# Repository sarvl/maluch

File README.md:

## mALUch - 16 bit simple CPU

mALUch is a simple 16 bit cpu, created mostly as a design exercise 

## Running Simulation and Compiling Tools
To compile simulator it is necessary to have ncurses installed  

```bash
cd Soft/Simulator
make
```

To run a file it's as simple as
```bash
./simulate path/to/file
```

## Assembler  
To use assembler it is necessary to have fasmg installed

The assembler is implemented as a fasmg .inc file, so to write your own program you have to have `include "path/to/maluch.inc"` included in your file.  
To just do `include "maluch.inc"` make sure to add the path to maluch.inc to an environment variable called INCLUDE.

To compile a program do
```bash
fasmg main.asm [output]
```
The output name is optional, the default is the name of the input file sans the extension.

## Physical Implementation
work in progress 😎

## Software Implementation
in Simulator/  
  
mostly straightforward implementation with no interesting quirks, type `help` for list of commands, use `tab` to switch between COMMANDS window and SCREEN window.

## Authors
[@sarvl](https://github.com/sarvl)  
[@Racuun](https://github.com/Racuun)

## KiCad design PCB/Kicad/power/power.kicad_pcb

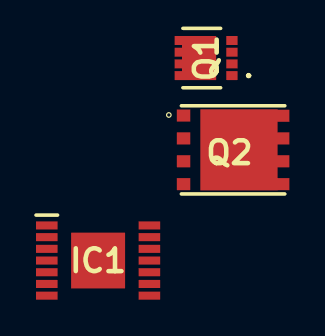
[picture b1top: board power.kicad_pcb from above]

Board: 2 copper layers, 3 parts (0 on the bottom side), 4 nets, no tracks yet.

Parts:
IC1: LM3150MH_NOPB; SOP65P640X110-15L
Q1: CSD17308Q3
Q2: CSD18531Q5A; Q5A

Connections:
unnamed: IC1.11 (HG), Q1.4 (G)
unnamed: IC1.13 (LG), Q2.4 (G)
unnamed: IC1.10 (SW), Q1.1 (S_1), Q1.2 (S_2), Q1.3 (S_3), Q2.5 (D_1), Q2.6 (D_2), Q2.7 (D_3), Q2.8 (D_4)
unnamed: Q2.1 (S_1), Q2.2 (S_2), Q2.3 (S_3)

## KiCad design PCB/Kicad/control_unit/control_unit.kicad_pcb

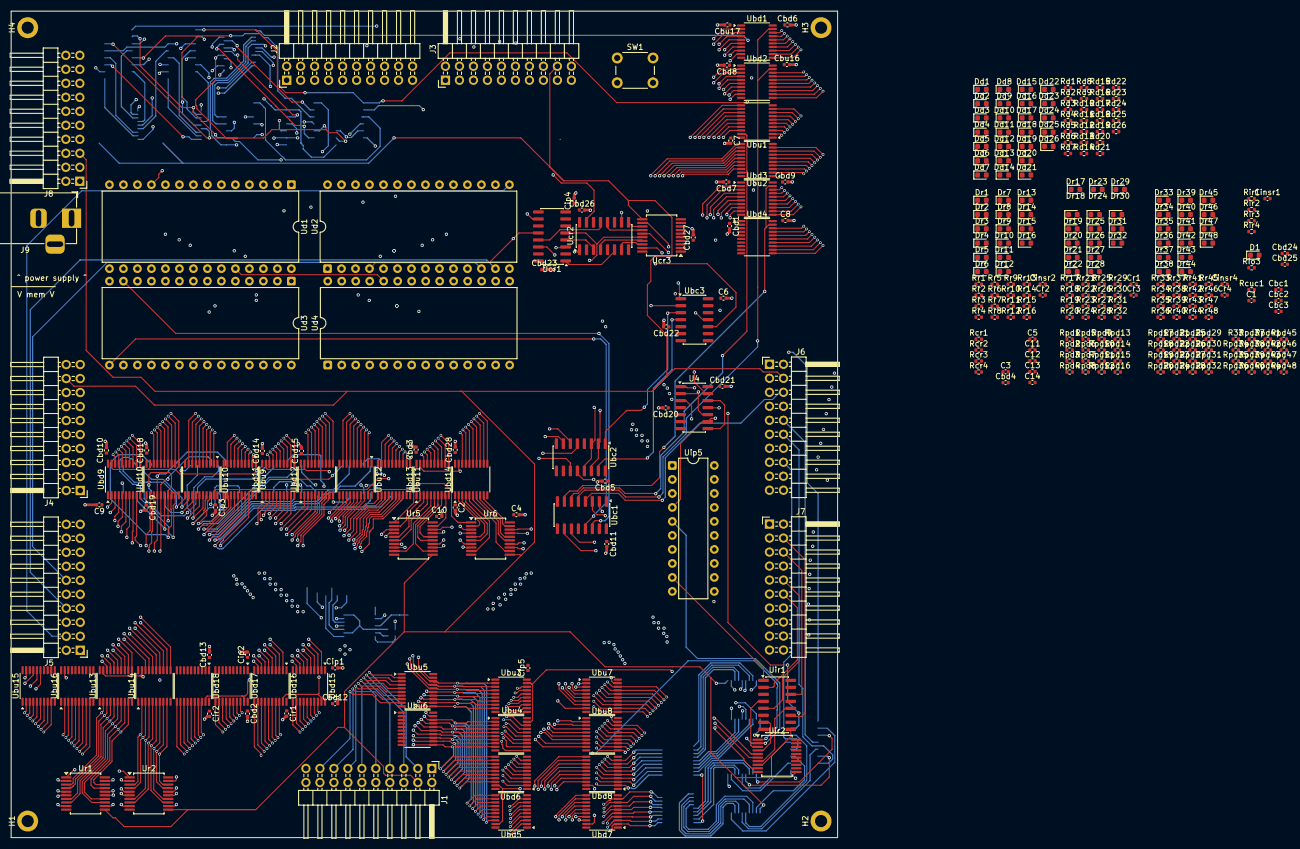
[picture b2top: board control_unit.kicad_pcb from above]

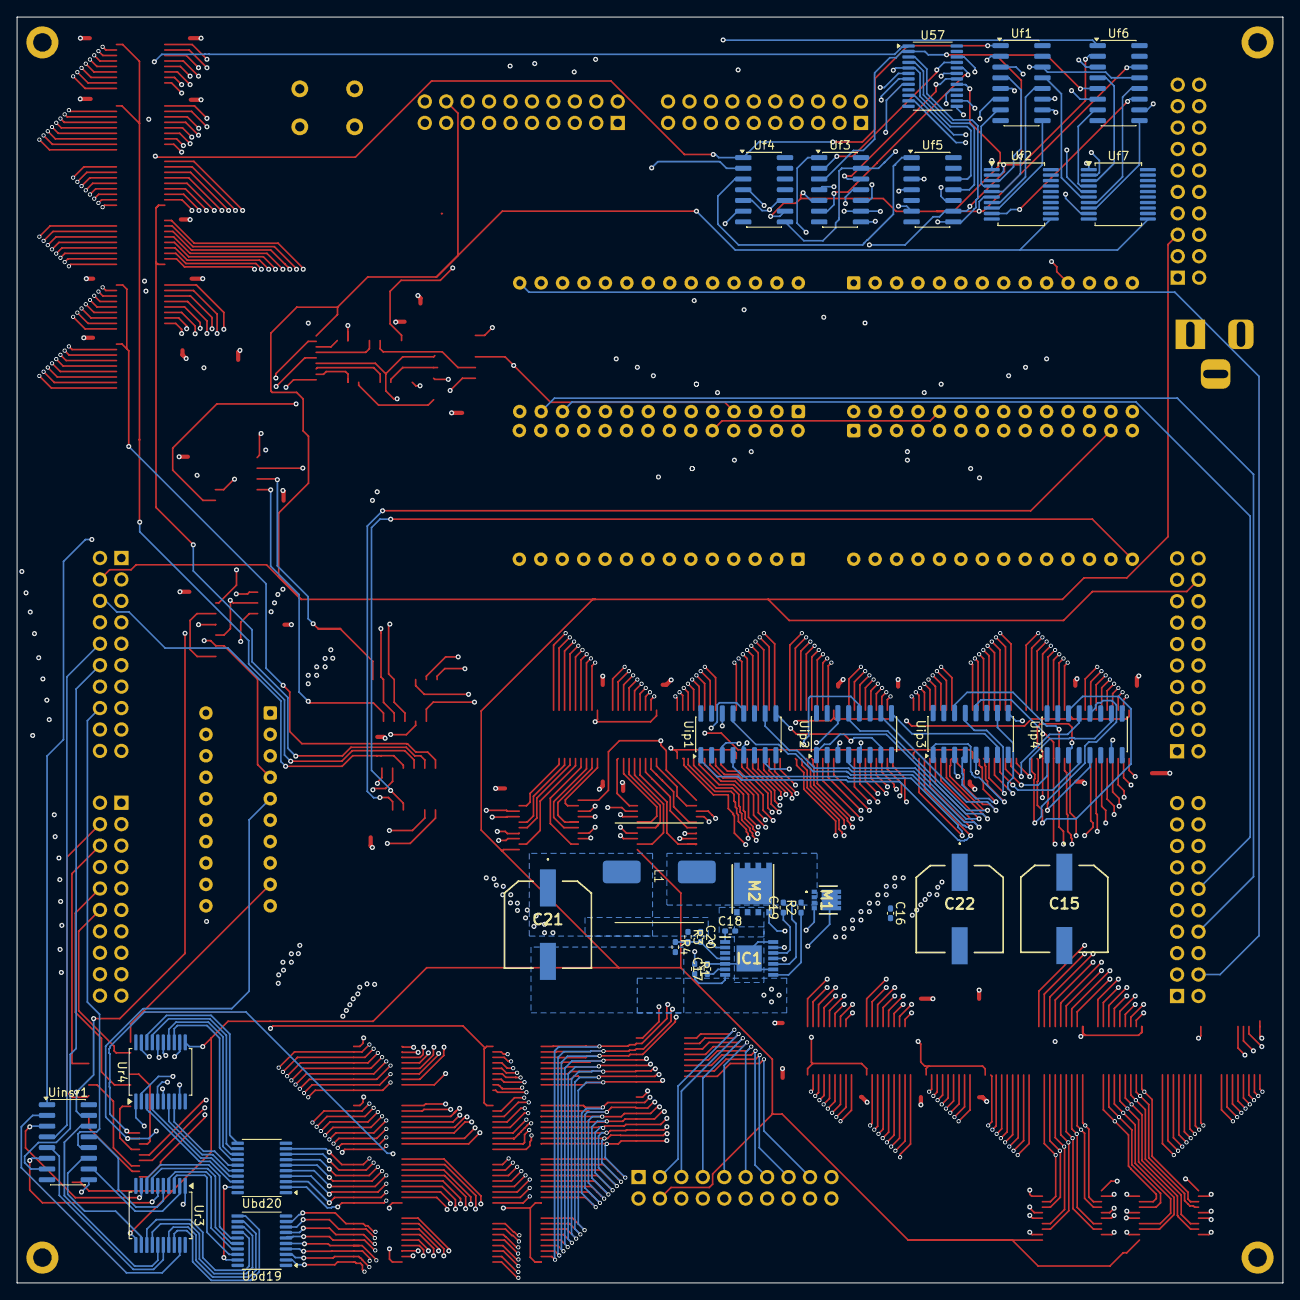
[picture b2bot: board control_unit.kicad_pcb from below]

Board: 6 copper layers, 150.0 x 150.0 mm, 365 parts (33 on the bottom side), 369 nets.

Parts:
C1, C2, C3, C4, C5, C6, C7, C8, C9, C10, C11, C12, C13, C14: 100nF; C_0402_1005Metric
C15, C22: 120uF; 16SVF1000M
C16: 100nF; C_0402_1005Metric_Pad0.74x0.62mm_HandSolder
C17: 15nF; R_0402_1005Metric_Pad0.72x0.64mm_HandSolder
C18: 1uF; R_0402_1005Metric_Pad0.72x0.64mm_HandSolder
C19: 470nF; R_0402_1005Metric_Pad0.72x0.64mm_HandSolder
C20: 430pF; R_0402_1005Metric_Pad0.72x0.64mm_HandSolder
C21: 150uF; 16SVF1000M
Cbc1, Cbc2, Cbc3: 100nF; C_0402_1005Metric
Cbd1, Cbd2, Cbd3, Cbd4, Cbd5, Cbd6, Cbd7, Cbd8, Cbd9, Cbd10, Cbd11, Cbd12, Cbd13, Cbd14, Cbd15, Cbd18, Cbd19, Cbd20, Cbd21, Cbd22, Cbd23, Cbd24, Cbd25, Cbd26, Cbd27, Cbd28: 100nF; C_0402_1005Metric
Cbu16, Cbu17: 100nF; C_0402_1005Metric
Cinsr1, Cinsr2, Cinsr4: 100nF; C_0402_1005Metric
Cip1, Cip2, Cip3, Cip4, Cip5: 100nF; C_0402_1005Metric
Cir1, Cir2: 100nF; C_0402_1005Metric
Cr1, Cr2, Cr3, Cr4: 100nF; C_0402_1005Metric
D1: green; LED_0603_1608Metric
Dd1, Dd2, Dd3, Dd4, Dd5, Dd6, Dd7, Dd8, Dd9, Dd10, Dd11, Dd12, Dd13, Dd14, Dd15, Dd16, Dd17, Dd18, Dd19, Dd20, Dd21, Dd22, Dd23, Dd24, Dd25, Dd26: yellow; LED_0603_1608Metric
Dr1, Dr2, Dr3, Dr4, Dr5, Dr6, Dr7, Dr8, Dr9, Dr10, Dr11, Dr12, Dr13, Dr14, Dr15, Dr16, Dr17, Dr18, Dr19, Dr20, Dr21, Dr22, Dr23, Dr24, Dr25, Dr26, Dr27, Dr28, Dr29, Dr30, Dr31, Dr32, Dr33, Dr34, Dr35, Dr36, Dr37, Dr38, Dr39, Dr40, Dr41, Dr42, Dr43, Dr44, Dr45, Dr46, Dr47, Dr48: red; LED_0603_1608Metric
H1, H2, H3, H4: MountingHole_Pad; MountingHole_2.2mm_M2_DIN965_Pad
IC1: LM3150MH_NOPB; SOP65P640X110-15L
J1, J2, J3, J4, J5, J6, J7, J8: in; PinHeader_2x10_P2.54mm_Horizontal
J9: Barrel_Jack_MountingPin; BarrelJack_Horizontal
L1: 3.3u; MLC1260
M1: CSD17308Q3
M2: CSD18531Q5A; Q5A
R1: 182kOhm; R_0402_1005Metric_Pad0.72x0.64mm_HandSolder
R2: 1.21kOhm; R_0402_1005Metric_Pad0.72x0.64mm_HandSolder
R3: 73.2kOhm; R_0402_1005Metric_Pad0.72x0.64mm_HandSolder
R4: 10kOhm; R_0402_1005Metric_Pad0.72x0.64mm_HandSolder
R33: 10k; R_0402_1005Metric
Rcr1, Rcr2, Rcr3, Rcr4: 10k; R_0402_1005Metric
Rcuc1: 10k; R_0402_1005Metric
Rd1, Rd2, Rd3, Rd4, Rd5, Rd6, Rd7, Rd8, Rd9, Rd10, Rd11, Rd12, Rd13, Rd14, Rd15, Rd16, Rd17, Rd18, Rd19, Rd20, Rd21, Rd22, Rd23, Rd24, Rd25, Rd26: 680; R_0402_1005Metric
Rio3: 680; R_0402_1005Metric
Rir1, Rir2, Rir3, Rir4: 10k; R_0402_1005Metric
Rpd1, Rpd2, Rpd3, Rpd4, Rpd5, Rpd6, Rpd7, Rpd8, Rpd9, Rpd10, Rpd11, Rpd12, Rpd13, Rpd14, Rpd15, Rpd16, Rpd17, Rpd18, Rpd19, Rpd20, Rpd21, Rpd22, Rpd23, Rpd24, Rpd25, Rpd26, Rpd27, Rpd28, Rpd29, Rpd30, Rpd31, Rpd32, Rpd34, Rpd35, Rpd36, Rpd37, Rpd38, Rpd39, Rpd40, Rpd41, Rpd42, Rpd43, Rpd44, Rpd45, Rpd46, Rpd47, Rpd48: 10k; R_0402_1005Metric
Rr1, Rr2, Rr3, Rr4, Rr5, Rr6, Rr7, Rr8, Rr9, Rr10, Rr11, Rr12, Rr13, Rr14, Rr15, Rr16, Rr17, Rr18, Rr19, Rr20, Rr21, Rr22, Rr23, Rr24, Rr25, Rr26, Rr27, Rr28, Rr29, Rr30, Rr31, Rr32, Rr33, Rr34, Rr35, Rr36, Rr37, Rr38, Rr39, Rr40, Rr41, Rr42, Rr43, Rr44, Rr45, Rr46, Rr47, Rr48: 680; R_0402_1005Metric
SW1: SW_Push; SW_PUSH_6mm_H4.3mm
U4: 7408; SO-14_3.9x8.65mm_P1.27mm
U57: 744067; TSSOP-24_4.4x7.8mm_P0.65mm
Ubc1, Ubc2: 74139; SOIC-16_3.9x9.9mm_P1.27mm
Ubc3: 7404; SO-14_3.9x8.65mm_P1.27mm
Ubd1, Ubd2, Ubd3, Ubd4, Ubd5, Ubd6, Ubd7, Ubd8, Ubd9, Ubd10, Ubd11, Ubd12, Ubd13, Ubd14, Ubd15, Ubd16, Ubd17, Ubd18, Ubd19, Ubd20: 74245; TSSOP-20_4.4x6.5mm_P0.65mm
Ubu1, Ubu2, Ubu3, Ubu4, Ubu5, Ubu6, Ubu7, Ubu8, Ubu9, Ubu10, Ubu11, Ubu12, Ubu13, Ubu14, Ubu15, Ubu16: 74245; TSSOP-20_4.4x6.5mm_P0.65mm
Ucr1: 74283; SOIC-16_3.9x9.9mm_P1.27mm
Ucr2: 74257; SOIC-16_3.9x9.9mm_P1.27mm
Ucr3: 74377; SSOP-20_5.3x7.2mm_P0.65mm
Ud1, Ud2, Ud3, Ud4: KM28C64A; DIP-28_W15.24mm
Uf1, Uf6: 74257; SOIC-16_3.9x9.9mm_P1.27mm
Uf2, Uf7: 74377; SSOP-20_5.3x7.2mm_P0.65mm
Uf3: 7404; SO-14_3.9x8.65mm_P1.27mm
Uf4: 7432; SO-14_3.9x8.65mm_P1.27mm
Uf5: 7486; SO-14_3.9x8.65mm_P1.27mm
Uinsr1: 74257; SOIC-16_3.9x9.9mm_P1.27mm
Uip1, Uip2, Uip3, Uip4: 74283; SOIC-16_3.9x9.9mm_P1.27mm
Uip5: ATF16V8Bxx-xxPU; DIP-20_W7.62mm
Uir1: 74257; SOIC-16_3.9x9.9mm_P1.27mm
Uir2: 74377; SSOP-20_5.3x7.2mm_P0.65mm
Ur1, Ur2, Ur3, Ur4, Ur5, Ur6: 74377; SSOP-20_5.3x7.2mm_P0.65mm

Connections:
/ControlUnit/alusrc0: Dd19.2 (A), Ubc1.14 (A0), Ud3.13 (I/O2)
/ControlUnit/alusrc1: Dd20.2 (A), Ubc1.13 (A1), Ud3.15 (I/O3)
/ControlUnit/buscntrl/srcbus0: Ubd5.18 (B0), Ubu3.2 (A0), Ubu5.18 (B0), Ubu11.18 (B0)
/ControlUnit/buscntrl/srcbus1: Ubd5.17 (B1), Ubu3.3 (A1), Ubu5.17 (B1), Ubu11.17 (B1)
/ControlUnit/buscntrl/srcbus2: Ubd5.16 (B2), Ubu3.4 (A2), Ubu5.16 (B2), Ubu11.16 (B2)
/ControlUnit/buscntrl/srcbus3: Ubd5.15 (B3), Ubu3.5 (A3), Ubu5.15 (B3), Ubu11.15 (B3)
/ControlUnit/buscntrl/srcbus4: Ubd5.14 (B4), Ubu3.6 (A4), Ubu5.14 (B4), Ubu11.14 (B4)
/ControlUnit/buscntrl/srcbus5: Ubd5.13 (B5), Ubu3.7 (A5), Ubu5.13 (B5), Ubu11.13 (B5)
/ControlUnit/buscntrl/srcbus6: Ubd5.12 (B6), Ubu3.8 (A6), Ubu5.12 (B6), Ubu11.12 (B6)
/ControlUnit/buscntrl/srcbus7: Ubd5.11 (B7), Ubu3.9 (A7), Ubu5.11 (B7), Ubu11.11 (B7)
/ControlUnit/buscntrl/srcbus8: Ubd6.18 (B0), Ubu4.2 (A0), Ubu6.18 (B0), Ubu12.18 (B0)
/ControlUnit/buscntrl/srcbus9: Ubd6.17 (B1), Ubu4.3 (A1), Ubu6.17 (B1), Ubu12.17 (B1)
/ControlUnit/buscntrl/srcbus10: Ubd6.16 (B2), Ubu4.4 (A2), Ubu6.16 (B2), Ubu12.16 (B2)
/ControlUnit/buscntrl/srcbus11: Ubd6.15 (B3), Ubu4.5 (A3), Ubu6.15 (B3), Ubu12.15 (B3)
/ControlUnit/buscntrl/srcbus12: Ubd6.14 (B4), Ubu4.6 (A4), Ubu6.14 (B4), Ubu12.14 (B4)
/ControlUnit/buscntrl/srcbus13: Ubd6.13 (B5), Ubu4.7 (A5), Ubu6.13 (B5), Ubu12.13 (B5)
/ControlUnit/buscntrl/srcbus14: Ubd6.12 (B6), Ubu4.8 (A6), Ubu6.12 (B6), Ubu12.12 (B6)
/ControlUnit/buscntrl/srcbus15: Ubd6.11 (B7), Ubu4.9 (A7), Ubu6.11 (B7), Ubu12.11 (B7)
/ControlUnit/buscntrl/~alu_membusen: Ubc1.11 (O1), Ubd7.19 (CE), Ubd8.19 (CE)
/ControlUnit/buscntrl/~alu_regbusen: Ubc1.10 (O2), Ubu7.19 (CE), Ubu8.19 (CE)
/ControlUnit/buscntrl/~mem_ipen: Ubc2.5 (O1), Ubd9.19 (CE), Ubd10.19 (CE)
/ControlUnit/buscntrl/~mem_ipnexten: Ubc2.6 (O2), Ubu9.19 (CE), Ubu10.19 (CE)
/ControlUnit/buscntrl/~mem_regbusen: Ubc2.7 (O3), Ubd11.19 (CE), Ubd12.19 (CE)
/ControlUnit/buscntrl/~mem_srcbusen: Ubc2.12 (O0), Ubu11.19 (CE), Ubu12.19 (CE)
/ControlUnit/buscntrl/~mem_tempregen: Ubc2.11 (O1), Ubd13.19 (CE), Ubd14.19 (CE)
/ControlUnit/buscntrl/~memsrc2: Ubc2.15 (E), Ubc3.4
/ControlUnit/buscntrl/~reg_alubusen: Ubc1.6 (O2), Ubu1.19 (CE), Ubu2.19 (CE)
/ControlUnit/buscntrl/~reg_iobusen: Ubc1.7 (O3), Ubd3.19 (CE), Ubd4.19 (CE)
/ControlUnit/buscntrl/~reg_membusen: Ubc1.5 (O1), Ubd1.19 (CE), Ubd2.19 (CE)
/ControlUnit/buscntrl/~src_regbusen: Ubc3.2, Ubu3.19 (CE), Ubu4.19 (CE)
/ControlUnit/cycle0: Ucr1.5 (A1), Ucr3.16 (Q6), Ud1.7 (A3), Ud2.7 (A3), Ud3.7 (A3), Ud4.7 (A3)
/ControlUnit/cycle1: Ucr1.3 (A2), Ucr3.19 (Q7), Ud1.6 (A4), Ud2.6 (A4), Ud3.6 (A4), Ud4.6 (A4)
/ControlUnit/cycle2: Ucr1.14 (A3), Ucr3.15 (Q5), Ud1.5 (A5), Ud2.5 (A5), Ud3.5 (A5), Ud4.5 (A5)
/ControlUnit/cycle3: Ucr1.12 (A4), Ucr3.12 (Q4), Ud1.4 (A6), Ud2.4 (A6), Ud3.4 (A6), Ud4.4 (A6)
/ControlUnit/flags/c: U57.17 (I14), Uf2.6 (Q2), Uf3.5, Uf4.9, Uf6.14 (I0c)
/ControlUnit/flags/nc: U57.20 (I11), Uf3.6
/ControlUnit/flags/no: U57.16 (I15), Uf3.4
/ControlUnit/flags/ns: U57.21 (I10), Uf3.2
/ControlUnit/flags/nz: U57.7 (I2), Uf3.8
/ControlUnit/flags/o: U57.2 (I7), Uf2.5 (Q1), Uf3.3, Uf5.10, Uf6.5 (I0b)
/ControlUnit/flags/s: U57.22 (I9), Uf2.2 (Q0), Uf3.1, Uf5.9, Uf6.2 (I0a)
/ControlUnit/flags/savedc: Uf1.13 (I1c), Uf7.6 (Q2)
/ControlUnit/flags/savedo: Uf1.6 (I1b), Uf7.5 (Q1)
/ControlUnit/flags/saveds: Uf1.3 (I1a), Uf7.2 (Q0)
/ControlUnit/flags/savedz: Uf1.10 (I1d), Uf7.9 (Q3)
/ControlUnit/flags/z: U57.8 (I1), Uf2.9 (Q3), Uf3.9, Uf4.5, Uf4.10, Uf6.11 (I0d)
/ControlUnit/flwe: Dd15.2 (A), Ud2.18 (I/O6), Uf4.2, Uf6.1 (S)
/ControlUnit/instructionregister/buffer_down/out0: Rpd1.1, Ubd19.18 (B0), Ur3.3 (D0)
/ControlUnit/instructionregister/buffer_down/out1: Rpd2.1, Ubd19.17 (B1), Ur3.4 (D1)
/ControlUnit/instructionregister/buffer_down/out2: Rpd3.1, Ubd19.16 (B2), Ur3.7 (D2)
/ControlUnit/instructionregister/buffer_down/out3: Rpd4.1, Ubd19.15 (B3), Ur3.8 (D3)
/ControlUnit/instructionregister/buffer_down/out4: Rpd5.1, Ubd19.14 (B4), Ur3.13 (D4)
/ControlUnit/instructionregister/buffer_down/out5: Rpd6.1, Ubd19.13 (B5), Ur3.14 (D5)
/ControlUnit/instructionregister/buffer_down/out6: Rpd7.1, Ubd19.12 (B6), Ur3.17 (D6)
/ControlUnit/instructionregister/buffer_down/out7: Rpd8.1, Ubd19.11 (B7), Ur3.18 (D7)
/ControlUnit/instructionregister/buffer_down/out8: Rpd9.1, Ubd20.18 (B0), Ur4.3 (D0)
/ControlUnit/instructionregister/buffer_down/out9: Rpd10.1, Ubd20.17 (B1), Ur4.4 (D1)
/ControlUnit/instructionregister/buffer_down/out10: Rpd11.1, Ubd20.16 (B2), Ur4.7 (D2)
/ControlUnit/instructionregister/buffer_down/out11: Rpd12.1, Ubd20.15 (B3), Ur4.8 (D3)
/ControlUnit/instructionregister/buffer_down/out12: Rpd13.1, Ubd20.14 (B4), Ur4.13 (D4)
/ControlUnit/instructionregister/buffer_down/out13: Rpd14.1, Ubd20.13 (B5), Ur4.14 (D5)
/ControlUnit/instructionregister/buffer_down/out14: Rpd15.1, Ubd20.12 (B6), Ur4.17 (D6)
/ControlUnit/instructionregister/buffer_down/out15: Rpd16.1, Ubd20.11 (B7), Ur4.18 (D7)
/ControlUnit/instructionregister/instr0: Dr17.2 (A), Uinsr1.10 (I1d), Ur3.2 (Q0)
/ControlUnit/instructionregister/instr1: Dr18.2 (A), Uinsr1.13 (I1c), Ur3.5 (Q1)
/ControlUnit/instructionregister/instr2: Dr19.2 (A), Uinsr1.6 (I1b), Ur3.6 (Q2)
/ControlUnit/instructionregister/instr3: Dr20.2 (A), Uinsr1.3 (I1a), Ur3.9 (Q3)
/ControlUnit/instructionregister/instr4: Dr21.2 (A), Uinsr1.11 (I0d), Ur3.12 (Q4)
/ControlUnit/instructionregister/instr5: Dr22.2 (A), Uinsr1.14 (I0c), Ur3.15 (Q5)
/ControlUnit/instructionregister/instr6: Dr23.2 (A), Uinsr1.5 (I0b), Ur3.16 (Q6)
/ControlUnit/instructionregister/instr7: Dr24.2 (A), Uinsr1.2 (I0a), Ur3.19 (Q7)
/ControlUnit/instructionregister/instr11: Dr28.2 (A), Uip1.7 (C0), Ur4.9 (Q3)
/ControlUnit/intidsaved0: Ubu15.17 (B1), Uir2.5 (Q1)
/ControlUnit/intidsaved1: Ubu15.16 (B2), Uir2.6 (Q2)
/ControlUnit/intidsaved2: Ubu15.15 (B3), Uir2.9 (Q3)
/ControlUnit/iosrc: Dd21.2 (A), Ubu5.19 (CE), Ubu6.19 (CE), Ud4.11 (I/O0)
/ControlUnit/ip0: Dr1.2 (A), Ubd9.2 (A0), Uip1.5 (A1), Ur1.2 (Q0)
/ControlUnit/ip1: Dr2.2 (A), Ubd9.3 (A1), Uip1.3 (A2), Ur1.5 (Q1)
/ControlUnit/ip2: Dr3.2 (A), Ubd9.4 (A2), Uip1.14 (A3), Ur1.6 (Q2)
/ControlUnit/ip3: Dr4.2 (A), Ubd9.5 (A3), Uip1.12 (A4), Ur1.9 (Q3)
/ControlUnit/ip4: Dr5.2 (A), Ubd9.6 (A4), Uip2.5 (A1), Ur1.12 (Q4)
/ControlUnit/ip5: Dr6.2 (A), Ubd9.7 (A5), Uip2.3 (A2), Ur1.15 (Q5)
/ControlUnit/ip6: Dr7.2 (A), Ubd9.8 (A6), Uip2.14 (A3), Ur1.16 (Q6)
/ControlUnit/ip7: Dr8.2 (A), Ubd9.9 (A7), Uip2.12 (A4), Ur1.19 (Q7)
/ControlUnit/ip8: Dr9.2 (A), Ubd10.2 (A0), Uip3.5 (A1), Ur2.2 (Q0)
/ControlUnit/ip9: Dr10.2 (A), Ubd10.3 (A1), Uip3.3 (A2), Ur2.5 (Q1)
/ControlUnit/ip10: Dr11.2 (A), Ubd10.4 (A2), Uip3.14 (A3), Ur2.6 (Q2)
/ControlUnit/ip11: Dr12.2 (A), Ubd10.5 (A3), Uip3.12 (A4), Ur2.9 (Q3)
/ControlUnit/ip12: Dr13.2 (A), Ubd10.6 (A4), Uip4.5 (A1), Ur2.12 (Q4)
/ControlUnit/ip13: Dr14.2 (A), Ubd10.7 (A5), Uip4.3 (A2), Ur2.15 (Q5)
/ControlUnit/ip14: Dr15.2 (A), Ubd10.8 (A6), Uip4.14 (A3), Ur2.16 (Q6)
/ControlUnit/ip15: Dr16.2 (A), Ubd10.9 (A7), Uip4.12 (A4), Ur2.19 (Q7)
/ControlUnit/ip/ipnew0: R33.1, Ubd15.18 (B0), Ubd17.18 (B0), Ubu13.2 (A0), Ubu15.2 (A0), Ur1.3 (D0)
/ControlUnit/ip/ipnew1: Rpd34.1, Ubd15.17 (B1), Ubd17.17 (B1), Ubu13.3 (A1), Ubu15.3 (A1), Ur1.4 (D1)
/ControlUnit/ip/ipnew2: Rpd35.1, Ubd15.16 (B2), Ubd17.16 (B2), Ubu13.4 (A2), Ubu15.4 (A2), Ur1.7 (D2)
/ControlUnit/ip/ipnew3: Rpd36.1, Ubd15.15 (B3), Ubd17.15 (B3), Ubu13.5 (A3), Ubu15.5 (A3), Ur1.8 (D3)
/ControlUnit/ip/ipnew4: Rpd37.1, Ubd15.14 (B4), Ubd17.14 (B4), Ubu13.6 (A4), Ubu15.6 (A4), Ur1.13 (D4)
/ControlUnit/ip/ipnew5: Rpd38.1, Ubd15.13 (B5), Ubd17.13 (B5), Ubu13.7 (A5), Ubu15.7 (A5), Ur1.14 (D5)
/ControlUnit/ip/ipnew6: Rpd39.1, Ubd15.12 (B6), Ubd17.12 (B6), Ubu13.8 (A6), Ubu15.8 (A6), Ur1.17 (D6)
/ControlUnit/ip/ipnew7: Rpd40.1, Ubd15.11 (B7), Ubd17.11 (B7), Ubu13.9 (A7), Ubu15.9 (A7), Ur1.18 (D7)
/ControlUnit/ip/ipnew8: Rpd41.1, Ubd16.18 (B0), Ubd18.18 (B0), Ubu14.2 (A0), Ubu16.2 (A0), Ur2.3 (D0)
/ControlUnit/ip/ipnew9: Rpd42.1, Ubd16.17 (B1), Ubd18.17 (B1), Ubu14.3 (A1), Ubu16.3 (A1), Ur2.4 (D1)
/ControlUnit/ip/ipnew10: Rpd43.1, Ubd16.16 (B2), Ubd18.16 (B2), Ubu14.4 (A2), Ubu16.4 (A2), Ur2.7 (D2)
/ControlUnit/ip/ipnew11: Rpd44.1, Ubd16.15 (B3), Ubd18.15 (B3), Ubu14.5 (A3), Ubu16.5 (A3), Ur2.8 (D3)
/ControlUnit/ip/ipnew12: Rpd45.1, Ubd16.14 (B4), Ubd18.14 (B4), Ubu14.6 (A4), Ubu16.6 (A4), Ur2.13 (D4)
/ControlUnit/ip/ipnew13: Rpd46.1, Ubd16.13 (B5), Ubd18.13 (B5), Ubu14.7 (A5), Ubu16.7 (A5), Ur2.14 (D5)
/ControlUnit/ip/ipnew14: Rpd47.1, Ubd16.12 (B6), Ubd18.12 (B6), Ubu14.8 (A6), Ubu16.8 (A6), Ur2.17 (D6)
/ControlUnit/ip/ipnew15: Rpd48.1, Ubd16.11 (B7), Ubd18.11 (B7), Ubu14.9 (A7), Ubu16.9 (A7), Ur2.18 (D7)
/ControlUnit/ip/~intidbusen: Ubu15.19 (CE), Ubu16.19 (CE), Uip5.15 (I/O)
/ControlUnit/ip/~ipincen: Ubd15.19 (CE), Ubd16.19 (CE), Uip5.12 (I/O)
/ControlUnit/ip/~membusen: Ubu13.19 (CE), Ubu14.19 (CE), Uip5.14 (I/O)
/ControlUnit/ip/~srcbusen: Ubd17.19 (CE), Ubd18.19 (CE), Uip5.13 (I/O)
/ControlUnit/ipnext0: Ubd15.2 (A0), Ubu9.18 (B0), Uip1.4 (S1)
/ControlUnit/ipnext1: Ubd15.3 (A1), Ubu9.17 (B1), Uip1.1 (S2)
/ControlUnit/ipnext2: Ubd15.4 (A2), Ubu9.16 (B2), Uip1.13 (S3)
/ControlUnit/ipnext3: Ubd15.5 (A3), Ubu9.15 (B3), Uip1.10 (S4)
/ControlUnit/ipnext4: Ubd15.6 (A4), Ubu9.14 (B4), Uip2.4 (S1)
/ControlUnit/ipnext5: Ubd15.7 (A5), Ubu9.13 (B5), Uip2.1 (S2)
/ControlUnit/ipnext6: Ubd15.8 (A6), Ubu9.12 (B6), Uip2.13 (S3)
/ControlUnit/ipnext7: Ubd15.9 (A7), Ubu9.11 (B7), Uip2.10 (S4)
/ControlUnit/ipnext8: Ubd16.2 (A0), Ubu10.18 (B0), Uip3.4 (S1)
/ControlUnit/ipnext9: Ubd16.3 (A1), Ubu10.17 (B1), Uip3.1 (S2)
/ControlUnit/ipnext10: Ubd16.4 (A2), Ubu10.16 (B2), Uip3.13 (S3)
/ControlUnit/ipnext11: Ubd16.5 (A3), Ubu10.15 (B3), Uip3.10 (S4)
/ControlUnit/ipnext12: Ubd16.6 (A4), Ubu10.14 (B4), Uip4.4 (S1)
/ControlUnit/ipnext13: Ubd16.7 (A5), Ubu10.13 (B5), Uip4.1 (S2)
/ControlUnit/ipnext14: Ubd16.8 (A6), Ubu10.12 (B6), Uip4.13 (S3)
/ControlUnit/ipnext15: Ubd16.9 (A7), Ubu10.11 (B7), Uip4.10 (S4)
/ControlUnit/isint: Ubd19.19 (CE), Ubd20.19 (CE), Uip5.5 (I4), Uir2.2 (Q0)
/ControlUnit/isjump: Dd13.2 (A), Ud2.16 (I/O4), Uip5.2 (I1)
/ControlUnit/isret: Dd8.2 (A), U4.9, Ud1.19 (I/O7), Uip5.4 (I3)
/ControlUnit/isstack: Dd25.2 (A), Ud3.16 (I/O4), Uinsr1.15 (OE)
/ControlUnit/memsrc0: Dd22.2 (A), Ubc2.2 (A0), Ubc2.14 (A0), Ud3.17 (I/O5)
/ControlUnit/memsrc1: Dd23.2 (A), Ubc2.3 (A1), Ubc2.13 (A1), Ud3.18 (I/O6)
/ControlUnit/memsrc2: Dd24.2 (A), Ubc2.1 (E), Ubc3.3, Ud3.19 (I/O7)
/ControlUnit/next_instr: Dd1.2 (A), U4.2, U4.10, Ubc3.11, Ud1.11 (I/O0)
/ControlUnit/opcode0: Dr29.2 (A), U57.13 (S3), Ud1.3 (A7), Ud2.3 (A7), Ud3.3 (A7), Ud4.3 (A7), Ur4.12 (Q4)
/ControlUnit/opcode1: Dr30.2 (A), Ud1.25 (A8), Ud2.25 (A8), Ud3.25 (A8), Ud4.25 (A8), Ur4.15 (Q5)
/ControlUnit/opcode2: Dr31.2 (A), Ud1.24 (A9), Ud2.24 (A9), Ud3.24 (A9), Ud4.24 (A9), Ur4.16 (Q6)
/ControlUnit/opcode3: Dr32.2 (A), Ud1.21 (A10), Ud2.21 (A10), Ud3.21 (A10), Ud4.21 (A10), Ur4.19 (Q7)
/ControlUnit/regds: Dd26.2 (A), Ud4.12 (I/O1), Uinsr1.1 (S)
/ControlUnit/regsrc0: Dd17.2 (A), Ubc1.2 (A0), Ud3.11 (I/O0)
/ControlUnit/regsrc1: Dd18.2 (A), Ubc1.3 (A1), Ud3.12 (I/O1)
/ControlUnit/rst: Rcuc1.1, SW1.2, Ucr2.15 (OE), Uip5.9 (I8), Uir1.1 (S)
/ControlUnit/should_jump: U57.1 (COM_I/O), Uip5.3 (I2)
/ControlUnit/srcsrc: Dd16.2 (A), Ubc3.1, Ubd5.19 (CE), Ubd6.19 (CE), Ud2.19 (I/O7)
/ControlUnit/tempreg0: Dr33.2 (A), Ubd13.2 (A0), Ur5.2 (Q0)
/ControlUnit/tempreg1: Dr34.2 (A), Ubd13.3 (A1), Ur5.5 (Q1)
/ControlUnit/tempreg2: Dr35.2 (A), Ubd13.4 (A2), Ur5.6 (Q2)
/ControlUnit/tempreg3: Dr36.2 (A), Ubd13.5 (A3), Ur5.9 (Q3)
/ControlUnit/tempreg4: Dr37.2 (A), Ubd13.6 (A4), Ur5.12 (Q4)
/ControlUnit/tempreg5: Dr38.2 (A), Ubd13.7 (A5), Ur5.15 (Q5)
/ControlUnit/tempreg6: Dr39.2 (A), Ubd13.8 (A6), Ur5.16 (Q6)
/ControlUnit/tempreg7: Dr40.2 (A), Ubd13.9 (A7), Ur5.19 (Q7)
/ControlUnit/tempreg8: Dr41.2 (A), Ubd14.2 (A0), Ur6.2 (Q0)
/ControlUnit/tempreg9: Dr42.2 (A), Ubd14.3 (A1), Ur6.5 (Q1)
/ControlUnit/tempreg10: Dr43.2 (A), Ubd14.4 (A2), Ur6.6 (Q2)
/ControlUnit/tempreg11: Dr44.2 (A), Ubd14.5 (A3), Ur6.9 (Q3)
/ControlUnit/tempreg12: Dr45.2 (A), Ubd14.6 (A4), Ur6.12 (Q4)
/ControlUnit/tempreg13: Dr46.2 (A), Ubd14.7 (A5), Ur6.15 (Q5)
/ControlUnit/tempreg14: Dr47.2 (A), Ubd14.8 (A6), Ur6.16 (Q6)
/ControlUnit/tempreg15: Dr48.2 (A), Ubd14.9 (A7), Ur6.19 (Q7)
/ControlUnit/~instr_load: Rd9.2, Ud2.11 (I/O0), Ur3.1 (~E), Ur4.1 (~E)
/ControlUnit/~next_instr: Ubc3.10, Ucr2.1 (S), Uir2.1 (~E), Ur1.1 (~E), Ur2.1 (~E)
/ControlUnit/~tempregwe: Rd14.2, Ud2.17 (I/O5), Ur5.1 (~E), Ur6.1 (~E)
/Power/BST: C19.1, IC1.12 (BST)
/Power/FB: C20.2, IC1.4 (FB), R3.2, R4.1
/Power/HG: IC1.11 (HG), M2.4 (G)
/Power/ICVCC: C18.1, IC1.1 (VCC)
/Power/ILIM: IC1.8 (ILIM), R2.1
/Power/LG: IC1.13 (LG), M1.4 (G)
/Power/RON: IC1.7 (RON), R1.2
/Power/SS: C17.1, IC1.6 (SS)
/Power/SW: C19.2, IC1.10 (SW), L1.1, M1.1 (S_1), M1.2 (S_2), M1.3 (S_3), M2.5 (D_1), M2.6 (D_2), M2.7 (D_3), M2.8 (D_4), R2.2
/Power/VIN: C15.1, C16.1, C22.1, IC1.2 (VIN), J9.1, M1.5 (D_1), M1.6 (D_2), M1.7 (D_3), M1.8 (D_4), M1.9 (D_5), R1.1
/alubus0: J3.17, Rpd17.1, Ubd7.18 (B0), Ubu1.18 (B0), Ubu7.2 (A0)
/alubus1: J3.15, Rpd18.1, Ubd7.17 (B1), Ubu1.17 (B1), Ubu7.3 (A1)
/alubus2: J3.13, Rpd19.1, Ubd7.16 (B2), Ubu1.16 (B2), Ubu7.4 (A2)
/alubus3: J3.11, Rpd20.1, Ubd7.15 (B3), Ubu1.15 (B3), Ubu7.5 (A3)
/alubus4: J3.9, Rpd21.1, Ubd7.14 (B4), Ubu1.14 (B4), Ubu7.6 (A4)
/alubus5: J3.7, Rpd22.1, Ubd7.13 (B5), Ubu1.13 (B5), Ubu7.7 (A5)
/alubus6: J3.5, Rpd23.1, Ubd7.12 (B6), Ubu1.12 (B6), Ubu7.8 (A6)
/alubus7: J3.3, Rpd24.1, Ubd7.11 (B7), Ubu1.11 (B7), Ubu7.9 (A7)
/alubus8: J2.17, Rpd25.1, Ubd8.18 (B0), Ubu2.18 (B0), Ubu8.2 (A0)
/alubus9: J2.15, Rpd26.1, Ubd8.17 (B1), Ubu2.17 (B1), Ubu8.3 (A1)
/alubus10: J2.13, Rpd27.1, Ubd8.16 (B2), Ubu2.16 (B2), Ubu8.4 (A2)
/alubus11: J2.11, Rpd28.1, Ubd8.15 (B3), Ubu2.15 (B3), Ubu8.5 (A3)
/alubus12: J2.9, Rpd29.1, Ubd8.14 (B4), Ubu2.14 (B4), Ubu8.6 (A4)
/alubus13: J2.7, Rpd30.1, Ubd8.13 (B5), Ubu2.13 (B5), Ubu8.7 (A5)
/alubus14: J2.5, Rpd31.1, Ubd8.12 (B6), Ubu2.12 (B6), Ubu8.8 (A6)
/alubus15: J2.3, Rpd32.1, Ubd8.11 (B7), Ubu2.11 (B7), Ubu8.9 (A7)
/aluop0: Dd2.2 (A), J2.18, Ud1.12 (I/O1)
/aluop1: Dd3.2 (A), J2.14, Ud1.13 (I/O2)
/aluop2: Dd4.2 (A), J2.8, Ud1.15 (I/O3)
/aluop3: Dd5.2 (A), J2.4, Ud1.16 (I/O4)
/clk: J1.4, J3.18, J4.18, J6.4, J8.3, J8.5, Ucr3.11 (CP), Uf2.11 (CP), Uf7.11 (CP), Uir2.11 (CP), Ur1.11 (CP), Ur2.11 (CP), Ur3.11 (CP), Ur4.11 (CP), Ur5.11 (CP), Ur6.11 (CP)
/fc: J3.10, Uf1.14 (I0c), Uf6.13 (I1c)
/fo: J3.6, Uf1.5 (I0b), Uf6.6 (I1b)
/fs: J3.4, Uf1.2 (I0a), Uf6.3 (I1a)
/fz: J3.12, Uf1.11 (I0d), Uf6.10 (I1d)
/int: J7.12, U4.1, Uir1.2 (I0a)
/intid0: J7.10, Uir1.5 (I0b)
/intid1: J7.6, Uir1.14 (I0c)
/intid2: J7.4, Uir1.11 (I0d)
/iobus0: J1.3, Ubd3.2 (A0), Ubu5.2 (A0)
/iobus1: J1.5, Ubd3.3 (A1), Ubu5.3 (A1)
/iobus2: J1.7, Ubd3.4 (A2), Ubu5.4 (A2)
/iobus3: J1.9, Ubd3.5 (A3), Ubu5.5 (A3)
/iobus4: J1.11, Ubd3.6 (A4), Ubu5.6 (A4)
/iobus5: J1.13, Ubd3.7 (A5), Ubu5.7 (A5)
/iobus6: J1.15, Ubd3.8 (A6), Ubu5.8 (A6)
/iobus7: J1.17, Ubd3.9 (A7), Ubu5.9 (A7)
/iocmd0: Dd6.2 (A), J1.16, Ud1.18 (I/O6)
/iocmd1: Dd7.2 (A), J1.18, Ud1.17 (I/O5)
/ioid0: Dr25.2 (A), J1.6, U4.13, U57.10 (S0), Ud1.10 (A0), Ud2.10 (A0), Ud3.10 (A0), Ud4.10 (A0), Ur4.2 (Q0)
/ioid1: Dr26.2 (A), J1.10, U57.11 (S1), Ud1.9 (A1), Ud2.9 (A1), Ud3.9 (A1), Ud4.9 (A1), Ur4.5 (Q1)
/ioid2: Dr27.2 (A), J1.12, U57.14 (S2), Ud1.8 (A2), Ud2.8 (A2), Ud3.8 (A2), Ud4.8 (A2), Ur4.6 (Q2)
/mask_restore: J7.18, U4.11, Uf1.1 (S), Uf4.1
/mask_save: J7.16, U4.3, Uf5.4
/membus0: J5.3, Ubd1.2 (A0), Ubd5.2 (A0), Ubd7.2 (A0), Ubd9.18 (B0), Ubd11.18 (B0), Ubd13.18 (B0), Ubd19.2 (A0), Ubu9.2 (A0), Ubu11.2 (A0), Ubu13.18 (B0), Ur5.3 (D0)
/membus1: J5.5, Ubd1.3 (A1), Ubd5.3 (A1), Ubd7.3 (A1), Ubd9.17 (B1), Ubd11.17 (B1), Ubd13.17 (B1), Ubd19.3 (A1), Ubu9.3 (A1), Ubu11.3 (A1), Ubu13.17 (B1), Ur5.4 (D1)
/membus2: J5.7, Ubd1.4 (A2), Ubd5.4 (A2), Ubd7.4 (A2), Ubd9.16 (B2), Ubd11.16 (B2), Ubd13.16 (B2), Ubd19.4 (A2), Ubu9.4 (A2), Ubu11.4 (A2), Ubu13.16 (B2), Ur5.7 (D2)
/membus3: J5.9, Ubd1.5 (A3), Ubd5.5 (A3), Ubd7.5 (A3), Ubd9.15 (B3), Ubd11.15 (B3), Ubd13.15 (B3), Ubd19.5 (A3), Ubu9.5 (A3), Ubu11.5 (A3), Ubu13.15 (B3), Ur5.8 (D3)
/membus4: J5.11, Ubd1.6 (A4), Ubd5.6 (A4), Ubd7.6 (A4), Ubd9.14 (B4), Ubd11.14 (B4), Ubd13.14 (B4), Ubd19.6 (A4), Ubu9.6 (A4), Ubu11.6 (A4), Ubu13.14 (B4), Ur5.13 (D4)
/membus5: J5.13, Ubd1.7 (A5), Ubd5.7 (A5), Ubd7.7 (A5), Ubd9.13 (B5), Ubd11.13 (B5), Ubd13.13 (B5), Ubd19.7 (A5), Ubu9.7 (A5), Ubu11.7 (A5), Ubu13.13 (B5), Ur5.14 (D5)
/membus6: J5.15, Ubd1.8 (A6), Ubd5.8 (A6), Ubd7.8 (A6), Ubd9.12 (B6), Ubd11.12 (B6), Ubd13.12 (B6), Ubd19.8 (A6), Ubu9.8 (A6), Ubu11.8 (A6), Ubu13.12 (B6), Ur5.17 (D6)
/membus7: J5.17, Ubd1.9 (A7), Ubd5.9 (A7), Ubd7.9 (A7), Ubd9.11 (B7), Ubd11.11 (B7), Ubd13.11 (B7), Ubd19.9 (A7), Ubu9.9 (A7), Ubu11.9 (A7), Ubu13.11 (B7), Ur5.18 (D7)
/membus8: J4.3, Ubd2.2 (A0), Ubd6.2 (A0), Ubd8.2 (A0), Ubd10.18 (B0), Ubd12.18 (B0), Ubd14.18 (B0), Ubd20.2 (A0), Ubu10.2 (A0), Ubu12.2 (A0), Ubu14.18 (B0), Ur6.3 (D0)
/membus9: J4.5, Ubd2.3 (A1), Ubd6.3 (A1), Ubd8.3 (A1), Ubd10.17 (B1), Ubd12.17 (B1), Ubd14.17 (B1), Ubd20.3 (A1), Ubu10.3 (A1), Ubu12.3 (A1), Ubu14.17 (B1), Ur6.4 (D1)
/membus10: J4.7, Ubd2.4 (A2), Ubd6.4 (A2), Ubd8.4 (A2), Ubd10.16 (B2), Ubd12.16 (B2), Ubd14.16 (B2), Ubd20.4 (A2), Ubu10.4 (A2), Ubu12.4 (A2), Ubu14.16 (B2), Ur6.7 (D2)
/membus11: J4.9, Ubd2.5 (A3), Ubd6.5 (A3), Ubd8.5 (A3), Ubd10.15 (B3), Ubd12.15 (B3), Ubd14.15 (B3), Ubd20.5 (A3), Ubu10.5 (A3), Ubu12.5 (A3), Ubu14.15 (B3), Ur6.8 (D3)
/membus12: J4.11, Ubd2.6 (A4), Ubd6.6 (A4), Ubd8.6 (A4), Ubd10.14 (B4), Ubd12.14 (B4), Ubd14.14 (B4), Ubd20.6 (A4), Ubu10.6 (A4), Ubu12.6 (A4), Ubu14.14 (B4), Ur6.13 (D4)
/membus13: J4.13, Ubd2.7 (A5), Ubd6.7 (A5), Ubd8.7 (A5), Ubd10.13 (B5), Ubd12.13 (B5), Ubd14.13 (B5), Ubd20.7 (A5), Ubu10.7 (A5), Ubu12.7 (A5), Ubu14.13 (B5), Ur6.14 (D5)
/membus14: J4.15, Ubd2.8 (A6), Ubd6.8 (A6), Ubd8.8 (A6), Ubd10.12 (B6), Ubd12.12 (B6), Ubd14.12 (B6), Ubd20.8 (A6), Ubu10.8 (A6), Ubu12.8 (A6), Ubu14.12 (B6), Ur6.17 (D6)
/membus15: J4.17, Ubd2.9 (A7), Ubd6.9 (A7), Ubd8.9 (A7), Ubd10.11 (B7), Ubd12.11 (B7), Ubd14.11 (B7), Ubd20.9 (A7), Ubu10.9 (A7), Ubu12.9 (A7), Ubu14.11 (B7), Ur6.18 (D7)
/memop0: Dd10.2 (A), J5.4, Ud2.15 (I/O3)
/memop1: Dd11.2 (A), J5.8, Ud2.13 (I/O2)
/memop2: Dd12.2 (A), J5.12, Ud2.12 (I/O1)
/regbus0: J7.17, Ubd1.18 (B0), Ubd3.18 (B0), Ubd11.2 (A0), Ubu1.2 (A0), Ubu3.18 (B0), Ubu7.18 (B0)
/regbus1: J7.15, Ubd1.17 (B1), Ubd3.17 (B1), Ubd11.3 (A1), Ubu1.3 (A1), Ubu3.17 (B1), Ubu7.17 (B1)
/regbus2: J7.13, Ubd1.16 (B2), Ubd3.16 (B2), Ubd11.4 (A2), Ubu1.4 (A2), Ubu3.16 (B2), Ubu7.16 (B2)
/regbus3: J7.11, Ubd1.15 (B3), Ubd3.15 (B3), Ubd11.5 (A3), Ubu1.5 (A3), Ubu3.15 (B3), Ubu7.15 (B3)
/regbus4: J7.9, Ubd1.14 (B4), Ubd3.14 (B4), Ubd11.6 (A4), Ubu1.6 (A4), Ubu3.14 (B4), Ubu7.14 (B4)
/regbus5: J7.7, Ubd1.13 (B5), Ubd3.13 (B5), Ubd11.7 (A5), Ubu1.7 (A5), Ubu3.13 (B5), Ubu7.13 (B5)
/regbus6: J7.5, Ubd1.12 (B6), Ubd3.12 (B6), Ubd11.8 (A6), Ubu1.8 (A6), Ubu3.12 (B6), Ubu7.12 (B6)
/regbus7: J7.3, Ubd1.11 (B7), Ubd3.11 (B7), Ubd11.9 (A7), Ubu1.9 (A7), Ubu3.11 (B7), Ubu7.11 (B7)
/regbus8: J6.17, Ubd2.18 (B0), Ubd4.18 (B0), Ubd12.2 (A0), Ubu2.2 (A0), Ubu4.18 (B0), Ubu8.18 (B0)
/regbus9: J6.15, Ubd2.17 (B1), Ubd4.17 (B1), Ubd12.3 (A1), Ubu2.3 (A1), Ubu4.17 (B1), Ubu8.17 (B1)
/regbus10: J6.13, Ubd2.16 (B2), Ubd4.16 (B2), Ubd12.4 (A2), Ubu2.4 (A2), Ubu4.16 (B2), Ubu8.16 (B2)
/regbus11: J6.11, Ubd2.15 (B3), Ubd4.15 (B3), Ubd12.5 (A3), Ubu2.5 (A3), Ubu4.15 (B3), Ubu8.15 (B3)
/regbus12: J6.9, Ubd2.14 (B4), Ubd4.14 (B4), Ubd12.6 (A4), Ubu2.6 (A4), Ubu4.14 (B4), Ubu8.14 (B4)
/regbus13: J6.7, Ubd2.13 (B5), Ubd4.13 (B5), Ubd12.7 (A5), Ubu2.7 (A5), Ubu4.13 (B5), Ubu8.13 (B5)
/regbus14: J6.5, Ubd2.12 (B6), Ubd4.12 (B6), Ubd12.8 (A6), Ubu2.8 (A6), Ubu4.12 (B6), Ubu8.12 (B6)
/regbus15: J6.3, Ubd2.11 (B7), Ubd4.11 (B7), Ubd12.9 (A7), Ubu2.9 (A7), Ubu4.11 (B7), Ubu8.11 (B7)
/regwe: J6.6, Ubc1.4 (O0)
/rid0: J6.18, Rir1.1, Uinsr1.9 (Zd)
/rid1: J6.16, Rir2.1, Uinsr1.12 (Zc)
/rid2: J6.12, Rir3.1, Uinsr1.7 (Zb)
/rid3: J6.10, Rir4.1, Uinsr1.4 (Za)
GND: C1.2, C2.2, C3.2, C4.2, C5.2, C6.2, C7.2, C8.2, C9.2, C10.2, C11.2, C12.2, C13.2, C14.2, C15.2, C16.2, C17.2, C18.2, C21.2, C22.2, Cbc1.2, Cbc2.2, Cbc3.2, Cbd1.2, Cbd2.2, Cbd3.2, Cbd4.2, Cbd5.2, Cbd6.2, Cbd7.2, Cbd8.2, Cbd9.2, Cbd10.2, Cbd11.2, Cbd12.2, Cbd13.2, Cbd14.2, Cbd15.2, Cbd18.2, Cbd19.2, Cbd20.2, Cbd21.2, Cbd22.2, Cbd23.2, Cbd24.2, Cbd25.2, Cbd26.2, Cbd27.2, Cbd28.2, Cbu16.2, Cbu17.2, Cinsr1.2, Cinsr2.2, Cinsr4.2, Cip1.2, Cip2.2, Cip3.2, Cip4.2, Cip5.2, Cir1.2, Cir2.2, Cr1.2, Cr2.2, Cr3.2, Cr4.2, H1.1 (1_1), H2.1 (1_1), H3.1 (1_1), H4.1 (1_1), IC1.5 (SGND_1), IC1.9 (SGND_2), IC1.14 (PGND), IC1.15 (EP), J1.2, J1.8, J1.14, J1.20, J2.2, J2.6, J2.10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
unnamed: D1.1 (K), Rio3.1
unnamed: Dd1.1 (K), Rd1.1
unnamed: Dd2.1 (K), Rd2.1
unnamed: Dd3.1 (K), Rd3.1
unnamed: Dd4.1 (K), Rd4.1
unnamed: Dd5.1 (K), Rd5.1
unnamed: Dd6.1 (K), Rd6.1
unnamed: Dd7.1 (K), Rd7.1
unnamed: Dd8.1 (K), Rd8.1
unnamed: Dd9.1 (K), Rd9.1
unnamed: Dd10.1 (K), Rd10.1
unnamed: Dd11.1 (K), Rd11.1
unnamed: Dd12.1 (K), Rd12.1
unnamed: Dd13.1 (K), Rd13.1
unnamed: Dd14.1 (K), Rd14.1
unnamed: Dd15.1 (K), Rd15.1
unnamed: Dd16.1 (K), Rd16.1
unnamed: Dd17.1 (K), Rd17.1
unnamed: Dd18.1 (K), Rd18.1
unnamed: Dd19.1 (K), Rd19.1
unnamed: Dd20.1 (K), Rd20.1
unnamed: Dd21.1 (K), Rd21.1
unnamed: Dd22.1 (K), Rd22.1
unnamed: Dd23.1 (K), Rd23.1
unnamed: Dd24.1 (K), Rd24.1
unnamed: Dd25.1 (K), Rd25.1
unnamed: Dd26.1 (K), Rd26.1
unnamed: Dr1.1 (K), Rr1.1
unnamed: Dr2.1 (K), Rr2.1
unnamed: Dr3.1 (K), Rr3.1
unnamed: Dr4.1 (K), Rr4.1
unnamed: Dr5.1 (K), Rr5.1
unnamed: Dr6.1 (K), Rr6.1
unnamed: Dr7.1 (K), Rr7.1
unnamed: Dr8.1 (K), Rr8.1
unnamed: Dr9.1 (K), Rr9.1
unnamed: Dr10.1 (K), Rr10.1
unnamed: Dr11.1 (K), Rr11.1
unnamed: Dr12.1 (K), Rr12.1
unnamed: Dr13.1 (K), Rr13.1
unnamed: Dr14.1 (K), Rr14.1
unnamed: Dr15.1 (K), Rr15.1
unnamed: Dr16.1 (K), Rr16.1
unnamed: Dr17.1 (K), Rr17.1
unnamed: Dr18.1 (K), Rr18.1
unnamed: Dr19.1 (K), Rr19.1
unnamed: Dr20.1 (K), Rr20.1
unnamed: Dr21.1 (K), Rr21.1
unnamed: Dr22.1 (K), Rr22.1
unnamed: Dr23.1 (K), Rr23.1
unnamed: Dr24.1 (K), Rr24.1
unnamed: Dr25.1 (K), Rr25.1
unnamed: Dr26.1 (K), Rr26.1
unnamed: Dr27.1 (K), Rr27.1
unnamed: Dr28.1 (K), Rr28.1
unnamed: Dr29.1 (K), Rr29.1
unnamed: Dr30.1 (K), Rr30.1
unnamed: Dr31.1 (K), Rr31.1
unnamed: Dr32.1 (K), Rr32.1
unnamed: Dr33.1 (K), Rr33.1
unnamed: Dr34.1 (K), Rr34.1
unnamed: Dr35.1 (K), Rr35.1
unnamed: Dr36.1 (K), Rr36.1
unnamed: Dr37.1 (K), Rr37.1
unnamed: Dr38.1 (K), Rr38.1
unnamed: Dr39.1 (K), Rr39.1
unnamed: Dr40.1 (K), Rr40.1
unnamed: Dr41.1 (K), Rr41.1
unnamed: Dr42.1 (K), Rr42.1
unnamed: Dr43.1 (K), Rr43.1
unnamed: Dr44.1 (K), Rr44.1
unnamed: Dr45.1 (K), Rr45.1
unnamed: Dr46.1 (K), Rr46.1
unnamed: Dr47.1 (K), Rr47.1
unnamed: Dr48.1 (K), Rr48.1
unnamed: U4.8, U4.12
unnamed: U57.6 (I3), Uf3.10
unnamed: U57.5 (I4), Uf4.6, Uf5.12
unnamed: U57.4 (I5), Uf5.11
unnamed: U57.3 (I6), Uf3.11, Uf4.4, Uf5.8
unnamed: U57.19 (I12), Uf3.13, Uf4.8
unnamed: U57.18 (I13), Uf3.12
unnamed: Ucr1.4 (S1), Ucr2.3 (I1a)
unnamed: Ucr1.1 (S2), Ucr2.6 (I1b)
unnamed: Ucr1.13 (S3), Ucr2.13 (I1c)
unnamed: Ucr1.10 (S4), Ucr2.10 (I1d)
unnamed: Rcr4.2, Ucr2.4 (Za), Ucr3.17 (D6)
unnamed: Rcr3.2, Ucr2.7 (Zb), Ucr3.18 (D7)
unnamed: Rcr2.2, Ucr2.12 (Zc), Ucr3.14 (D5)
unnamed: Rcr1.2, Ucr2.9 (Zd), Ucr3.13 (D4)
unnamed: Uf1.4 (Za), Uf2.3 (D0)
unnamed: Uf1.7 (Zb), Uf2.4 (D1)
unnamed: Uf1.12 (Zc), Uf2.7 (D2)
unnamed: Uf1.9 (Zd), Uf2.8 (D3)
unnamed: Uf2.1 (~E), Uf5.3
unnamed: Uf4.3, Uf5.1
unnamed: Uf6.4 (Za), Uf7.3 (D0)
unnamed: Uf6.7 (Zb), Uf7.4 (D1)
unnamed: Uf6.12 (Zc), Uf7.7 (D2)
unnamed: Uf6.9 (Zd), Uf7.8 (D3)
unnamed: Uf5.6, Uf7.1 (~E)
unnamed: Uip1.9 (C4), Uip2.7 (C0)
unnamed: Uip2.9 (C4), Uip3.7 (C0)
unnamed: Uip3.9 (C4), Uip4.7 (C0)
unnamed: Uir1.4 (Za), Uir2.3 (D0)
unnamed: Uir1.7 (Zb), Uir2.4 (D1)
unnamed: Uir1.12 (Zc), Uir2.7 (D2)
unnamed: Uir1.9 (Zd), Uir2.8 (D3)
VCC: C1.1, C2.1, C3.1, C4.1, C5.1, C6.1, C7.1, C8.1, C9.1, C10.1, C11.1, C12.1, C13.1, C14.1, C20.1, C21.1, Cbc1.1, Cbc2.1, Cbc3.1, Cbd1.1, Cbd2.1, Cbd3.1, Cbd4.1, Cbd5.1, Cbd6.1, Cbd7.1, Cbd8.1, Cbd9.1, Cbd10.1, Cbd11.1, Cbd12.1, Cbd13.1, Cbd14.1, Cbd15.1, Cbd18.1, Cbd19.1, Cbd20.1, Cbd21.1, Cbd22.1, Cbd23.1, Cbd24.1, Cbd25.1, Cbd26.1, Cbd27.1, Cbd28.1, Cbu16.1, Cbu17.1, Cinsr1.1, Cinsr2.1, Cinsr4.1, Cip1.1, Cip2.1, Cip3.1, Cip4.1, Cip5.1, Cir1.1, Cir2.1, Cr1.1, Cr2.1, Cr3.1, Cr4.1, D1.2 (A), Dd9.2 (A), Dd14.2 (A), J1.1, J1.19, J2.1, J2.19, J3.1, J3.19, J4.1, J4.19, J5.1, J5.19, J6.1, J6.19, J7.1, J7.19, J8.9, J8.11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
